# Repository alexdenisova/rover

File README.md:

# Rover

An STM32 + ESP32 remote controller for a Yandex Rover toy that executes voice commands: "Forward", "Backward", "Right", "Left", "Spin", "Open", "Close".

As OpenAI's Whisper is rather slow at transcribing the audio, it takes several seconds for the rover to react to the oral command. In the future, I plan to train my own speech-to-text model in the hopes of making it quicker.

## How it works

The user says one of the commands, which is recorded by the MAX9814 microphone either onto the SD card or to the ESP32. The ESP32 creates a WAV file from the audio and sends it to the "Speech-to-Text" server that uses OpenAI's Whisper to transcribe the audio. Then, based on the command received, the STM32 sends an IR signal to the rover, who then completes the command.

## Video

In the demonstration, I give the command "Forward". The rover takes several seconds to react, as the speech-to-text model is rather slow at transcribing.

https://github.com/user-attachments/assets/662a4837-75a4-4f81-b607-461e728f610d

## Photos

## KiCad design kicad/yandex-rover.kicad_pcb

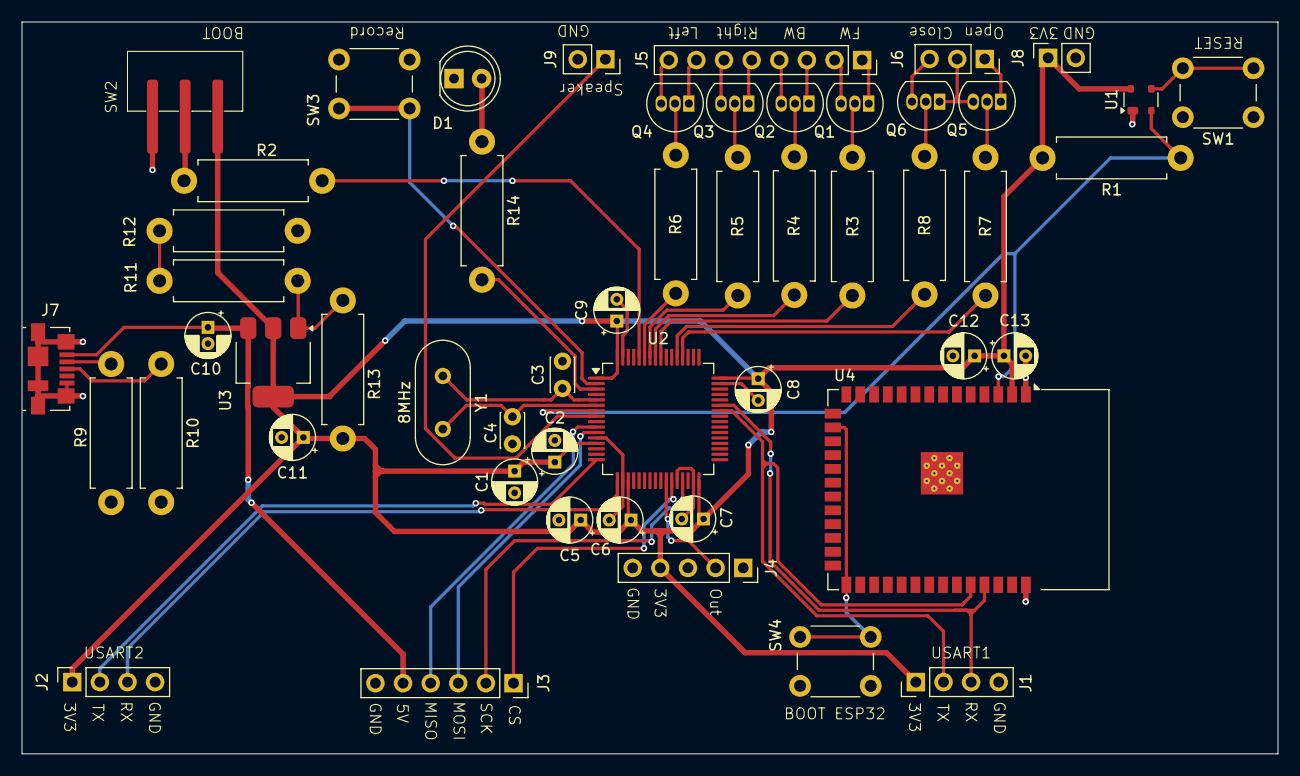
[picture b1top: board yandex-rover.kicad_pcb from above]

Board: 2 copper layers, 115.5 x 67.3 mm, 52 parts (0 on the bottom side), 49 nets.

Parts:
C1: 1uF; CP_Radial_D4.0mm_P2.00mm
C2, C6, C7, C8, C9, C13: 0.1uF; CP_Radial_D4.0mm_P2.00mm
C3, C4: 10pF; C_Disc_D3.0mm_W2.0mm_P2.50mm
C5: 4.7uF; CP_Radial_D4.0mm_P2.00mm
C10: 10uF; CP_Radial_D4.0mm_P1.50mm
C11, C12: 22uF; CP_Radial_D4.0mm_P2.00mm
D1: Recording; LED_D5.0mm
J1: USART1; PinHeader_1x04_P2.54mm_Vertical
J2: USART2; PinSocket_1x04_P2.54mm_Vertical
J3: microSD Module; PinSocket_1x06_P2.54mm_Vertical
J4: MAX9814; PinSocket_1x05_P2.54mm_Vertical
J5: Rover Directions; PinSocket_1x08_P2.54mm_Vertical
J6: Rover Lid; PinSocket_1x03_P2.54mm_Vertical
J7: USB_B_Micro; USB_Micro-B_Molex_47346-0001
J8: Rover Power; PinSocket_1x02_P2.54mm_Vertical
J9: Rover Speaker; PinSocket_1x02_P2.54mm_Vertical
Q1, Q2, Q3, Q4, Q5, Q6: TO-92_Inline
R1: 100k; R_Axial_DIN0411_L9.9mm_D3.6mm_P12.70mm_Horizontal
R2: 10k; R_Axial_DIN0411_L9.9mm_D3.6mm_P12.70mm_Horizontal
R3, R4, R5, R6, R7, R8, R14: 1k; R_Axial_DIN0411_L9.9mm_D3.6mm_P12.70mm_Horizontal
R9, R10: 20k; R_Axial_DIN0411_L9.9mm_D3.6mm_P12.70mm_Horizontal
R11: 20R; R_Axial_DIN0411_L9.9mm_D3.6mm_P12.70mm_Horizontal
R12: 750R; R_Axial_DIN0411_L9.9mm_D3.6mm_P12.70mm_Horizontal
R13: 470R; R_Axial_DIN0411_L9.9mm_D3.6mm_P12.70mm_Horizontal
SW1: RESET; SW_PUSH_6mm_H4.3mm
SW2: BOOT; KLS7-SS-12F19-G5
SW3: Recording; SW_PUSH_6mm
SW4: Boot ESP32; SW_PUSH_6mm
U1: MAX811SEUS+T; SOT-143
U2: STM32F401RETx; LQFP-64_10x10mm_P0.5mm
U3: AMS1117; SOT-223-3_TabPin2
U4: ESP32-S3-WROOM-1
Y1: 8MHz; Crystal_HC49-4H_Vertical

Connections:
+3.3V: C1.1, C2.1, C5.1, C6.1, C7.1, C8.1, C9.1, C11.1, C12.1, C13.1, J1.1, J2.1, J4.4, J8.1, R1.2, R13.1, SW2.3 (C), U1.4 (VCC), U2.1 (VBAT), U2.13 (VREF+), U2.19 (VDD), U2.32 (VDD), U2.48 (VDD), U2.64 (VDD), U3.2 (VO), U4.2 (3V3)
+5V: C10.1, J3.5, J7.1 (VBUS), U3.3 (VI)
/BOOT ESP32: SW4.2, U4.16 (IO46), U4.27 (IO0)
/BOOT STM32: R2.2, U2.60 (BOOT0)
/Backward_1: J5.3, Q2.1 (C)
/Backward_2: J5.4, Q2.3 (E)
/Close_1: J6.3, Q6.3 (E)
/Forward_1: J5.1, Q1.1 (C)
/Forward_2: J5.2, Q1.3 (E)
/Left_1: J5.7, Q4.1 (C)
/Left_2: J5.8, Q4.3 (E)
/Open_1: J6.1, Q5.1 (C)
/Open_Close: J6.2, Q5.3 (E), Q6.1 (C)
/Reset: R1.1, U1.2 (~RESET), U2.7 (NRST), U4.3 (EN)
/Right_1: J5.5, Q3.1 (C)
/Right_2: J5.6, Q3.3 (E)
/Rover Backward: R4.1, U2.57 (PB5)
/Rover Close: R8.1, U2.53 (PC12)
/Rover Forward: R3.1, U2.56 (PB4)
/Rover Left: R6.1, U2.59 (PB7)
/Rover Open: R7.1, U2.52 (PC11)
/Rover Right: R5.1, U2.58 (PB6)
/SD CS: J3.1, U2.27 (PB1)
/SD MISO: J3.4, U2.10 (PC2)
/SD MOSI: J3.3, U2.11 (PC3)
/SD SCK: J3.2, U2.29 (PB10)
/Speaker: J9.1, U2.8 (PC0)
/USART1_RX: J1.3, U2.43 (PA10), U4.37 (TXD0)
/USART1_TX: J1.2, U2.42 (PA9), U4.36 (RXD0)
/USART2_RX: J2.3, U2.17 (PA3)
/USART2_TX: J2.2, U2.16 (PA2)
/audio: J4.2, U2.26 (PB0)
GND: C1.2, C2.2, C3.2, C4.2, C5.2, C6.2, C7.2, C8.2, C9.2, C10.2, C11.2, C12.2, C13.2, D1.1 (K), J1.4, J2.4, J3.6, J4.5, J7.5 (GND), J7.6 (Shield), J8.2, J9.2, R9.2, R10.2, R12.2, SW1.1, SW2.1 (A), SW3.1, SW4.1, U1.1 (GND), U2.12 (VSSA), U2.18 (VSS), U2.28 (PB2), U2.31 (VSS), U2.47 (VSS), U2.63 (VSS), U4.1 (GND), U4.40 (GND), U4.41 (GND)
unnamed: D1.2 (A), R14.1
unnamed: J7.3 (D+), R10.1
unnamed: J7.2 (D-), R9.1
unnamed: Q1.2 (B), R3.2
unnamed: Q2.2 (B), R4.2
unnamed: Q3.2 (B), R5.2
unnamed: Q4.2 (B), R6.2
unnamed: Q5.2 (B), R7.2
unnamed: Q6.2 (B), R8.2
unnamed: R11.2, R12.1
unnamed: R2.1, SW2.2 (B)
unnamed: SW1.2, U1.3 (~MR)
unnamed: SW3.2, U2.2 (PC13)
unnamed: C3.1, U2.5 (PH0), Y1.1
unnamed: C4.1, U2.6 (PH1), Y1.2
unnamed: R11.1, R13.2, U3.1 (ADJ)

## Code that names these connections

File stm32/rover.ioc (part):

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Mcu.Name=STM32F401R(D-E)Tx
Mcu.Package=LQFP64
Mcu.UserName=STM32F401RETx
PA0-WKUP.Signal=ADCx_IN0
PA10.Mode=Asynchronous
PA10.Signal=USART1_RX
PA13.GPIOParameters=GPIO_Label
PA13.GPIO_Label=TMS
PA13.Mode=Serial_Wire
PA13.Signal=SYS_JTMS-SWDIO
PA14.GPIOParameters=GPIO_Label
PA14.GPIO_Label=TCK
PA14.Mode=Serial_Wire
PA14.Signal=SYS_JTCK-SWCLK
PA2.GPIOParameters=GPIO_Speed,GPIO_PuPd,GPIO_Label,GPIO_Mode
PA2.GPIO_Label=USART_TX
PA2.GPIO_Mode=GPIO_MODE_AF_PP
PA2.GPIO_PuPd=GPIO_NOPULL
PA2.GPIO_Speed=GPIO_SPEED_FREQ_LOW
PA2.Mode=Asynchronous
PA2.Signal=USART2_TX
PA3.GPIOParameters=GPIO_Speed,GPIO_PuPd,GPIO_Label,GPIO_Mode
PA3.GPIO_Label=USART_RX
PA3.GPIO_Mode=GPIO_MODE_AF_PP
PA3.GPIO_PuPd=GPIO_NOPULL
PA3.GPIO_Speed=GPIO_SPEED_FREQ_LOW
PA3.Mode=Asynchronous
PA3.Signal=USART2_RX
PA9.Mode=Asynchronous
PA9.Signal=USART1_TX
PB0.Signal=ADCx_IN8
PB1.GPIOParameters=GPIO_Label
PB1.GPIO_Label=SD_CS
PB1.Signal=GPIO_Output
PB10.Mode=Full_Duplex_Master
PB10.Signal=SPI2_SCK
PB4.GPIOParameters=GPIO_PuPd,GPIO_Label
PB4.GPIO_Label=Rover_Forward
PB4.GPIO_PuPd=GPIO_PULLDOWN
PB4.Signal=GPIO_Output
PB5.GPIOParameters=GPIO_PuPd,GPIO_Label
PB5.GPIO_Label=Rover_Backward
PB5.GPIO_PuPd=GPIO_PULLDOWN
PB5.Signal=GPIO_Output
PB6.GPIOParameters=GPIO_PuPd,GPIO_Label
PB6.GPIO_Label=Rover_Right
PB6.GPIO_PuPd=GPIO_PULLDOWN
PB6.Signal=GPIO_Output
PB7.GPIOParameters=GPIO_PuPd,GPIO_Label
PB7.GPIO_Label=Rover_Left
PB7.GPIO_PuPd=GPIO_PULLDOWN
PB7.Signal=GPIO_Output
PC0.GPIOParameters=GPIO_PuPd,GPIO_Label
PC0.GPIO_Label=Recording_LED
PC0.GPIO_PuPd=GPIO_PULLDOWN
PC0.Signal=GPIO_Output
PC11.GPIOParameters=GPIO_PuPd,GPIO_Label
PC11.GPIO_Label=Rover_Open
PC11.GPIO_PuPd=GPIO_PULLDOWN
PC11.Signal=GPIO_Output
PC12.GPIOParameters=GPIO_PuPd,GPIO_Label
PC12.GPIO_Label=Rover_Close
PC12.GPIO_PuPd=GPIO_PULLDOWN
PC12.Signal=GPIO_Output
PC13-ANTI_TAMP.GPIOParameters=GPIO_PuPd,GPIO_ModeDefaultEXTI
PC13-ANTI_TAMP.GPIO_ModeDefaultEXTI=GPIO_MODE_IT_FALLING
PC13-ANTI_TAMP.GPIO_PuPd=GPIO_PULLUP
PC13-ANTI_TAMP.Signal=GPXTI13
PC2.Mode=Full_Duplex_Master
PC2.Signal=SPI2_MISO
PC3.Mode=Full_Duplex_Master
PC3.Signal=SPI2_MOSI
PH0\ -\ OSC_IN.Mode=HSE-External-Clock-Source
PH0\ -\ OSC_IN.Signal=RCC_OSC_IN
PH1\ -\ OSC_OUT.Mode=HSE-External-Clock-Source
PH1\ -\ OSC_OUT.Signal=RCC_OSC_OUT
RCC.HSE_VALUE=8000000
RCC.SYSCLKFreq_VALUE=84000000
RCC.SYSCLKSource=RCC_SYSCLKSOURCE_PLLCLK
board=NUCLEO-F401RE
boardIOC=true

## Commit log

2025-08-03 testing ci
2025-08-03 test
2025-08-03 New package version - 25.8.0
2025-08-03 added speech-to-text
2025-08-03 New package version - 25.8.1
2025-08-03 clean up
2025-08-06 logs
2025-08-06 formatting
2025-08-06 ci fix
2025-08-06 added description
2025-08-06 added docs
2025-08-08 New package version - 25.8.2
2025-08-08 added chunk processing
2025-08-24 added esp32 code
2025-08-24 New package version - 25.8.3
2025-09-07 New package version - 25.9.0
2025-09-10 New package version - 25.9.1
2025-09-10 New package version - 25.9.2
2025-09-10 New package version - 25.9.3
2025-09-10 New package version - 25.9.4
2025-09-10 New package version - 25.9.5
2025-10-28 final
2025-10-28 New package version - 25.10.0
2025-10-28 New package version - 25.10.1
2026-01-07 added stm32, esp32, kicad
2026-01-07 New package version - 26.1.0
2026-01-07 changed stm32 pins
